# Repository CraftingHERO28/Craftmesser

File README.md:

# DIY Room Air Quality Monitor

I wanted to build a solid, reliable indoor air quality monitor to keep track of CO₂ levels, temperature, and humidity in my room. A lot of cheap commercial monitors use estimated VOC sensors instead of actual optical sensors, so I decided to design my own board around an Arduino Nano and an NDIR MH-Z19B sensor.

Through consistent through-hole (THT) construction and thermal decoupling, it delivers precise readings without self-heating distortion.

---

## How it Works & Hardware Choices

The setup is built completely with THT components on socket headers so everything stays easy to solder and swap out if needed:

* **Arduino Nano v3.x** handling the logic.
* **MH-Z19B** for actual NDIR CO₂ measurement.
* **DHT22 / AM2302** for temperature and humidity.
* **0.96" I2C OLED** for displaying live data.
* **Decoupling & Pull-up:** A `100nF` ceramic capacitor and a `100µF` electrolytic capacitor smooth out voltage drops when the CO₂ sensor warms up, paired with a `10kΩ` pull-up resistor for the DHT data line.

---

## Bill of Materials (BOM)

---

## Wiring Diagram

All components share a common `5V` and `GND` rail decoupled by the `100µF` electrolytic and `100nF` ceramic capacitors.

```text
                       +-----------------------+
                       |     ARDUINO NANO      |
                       |                       |
   +------------------>| 5V                 D2 |<---[10kΩ]---+--- 5V
   |   +-------------->| GND                   |             |
   |   |               |                    D3 |<---+        |
   |   |               |                    D4 |---+|        |
   |   |               |                    A4 |<--||---+    |
   |   |               |                    A5 |<--||--+|    |
   |   |               +-----------------------+   ||  ||    |
   |   |                                           ||  ||    |
   |   |   +---------------------------------------++  ||    |
   |   |   |   +---------------------------------------++    |
   |   |   |   |                                             |
   |   |   |   |       +-----------------------+             |
   |   |   |   |       |    DHT22 / AM2302     |             |
   +---|---|---|------>| VCC (Pin 1)           |             |
   |   |   |   |   +-->| DATA (Pin 2)          |<------------+
   |   +---|---|---|-->| GND (Pin 4)           |
   |   |   |   |   |   +-----------------------+
   |   |   |   |   |
   |   |   |   |   |   +-----------------------+
   |   |   |   |   |   |   MH-Z19B CO2 Sensor  |
   +---|---|---|------>| VIN (5V)              |
   |   +---|---|---|-->| GND                   |
   |   |   +---|---|-->| TX  (connects to D3)  |
   |   |   |   |   |   | RX  (connects to D4)  |
   |   |   |   |   |   +-----------------------+
   |   |   |   |   |
   |   |   |   |   |   +-----------------------+
   |   |   |   |   |   |   0.96" I2C OLED      |
   +---|---|---|------>| VCC                   |
   |   +---|---|---|-->| GND                   |
   |   |   |   +---|-->| SDA (connects to A4)  |
   |   |   |   |   +-->| SCL (connects to A5)  |
   |   |   |   |       +-----------------------+
   |   |   |   |
  [===] [===]  (Power Filtering across 5V & GND: 100µF Elko + 100nF Ceramic)
```

---

## How to Build It

### 1. Order the PCBs & Parts
* Export the Gerber files from the KiCad project and upload the `.zip` archive to **JLCPCB** (standard 2-layer FR4, 1.6mm thickness).
* Order all electronic components using the Reichelt links in the BOM table above.

### 2. Solder the Board (Lowest to Tallest)
1. **Passive Components:** Solder the `10kΩ` pull-up resistor and the `100nF` ceramic capacitor flat against the PCB.
2. **Socket Headers:** Solder the two `1x15` female headers for the Arduino Nano and the three `1x4` headers for the OLED, DHT22, and MH-Z19B. *Tip: Plug the headers onto the Arduino/modules first to keep them aligned while soldering.*
3. **Electrolytic Capacitor:** Solder the `100µF` capacitor into place, paying close attention to polarity (the striped side goes to `GND`).
4. **Insert Modules:** Once soldering is complete and checked for bridges, plug the Arduino Nano, OLED display, DHT22, and MH-Z19B into their respective sockets. Make sure the DHT22 sits cleanly at the edge of the board for accurate thermal isolation.

### 3. Flash the Firmware
1. Download and open the **Arduino IDE**.
2. Open the Library Manager (`Ctrl + Shift + I`) and install:
   * `Adafruit SSD1306`
   * `Adafruit GFX Library`
   * `DHT sensor library` (by Adafruit)
3. Connect the Arduino Nano via USB, select **Arduino Nano** (and **ATmega328P (Old Bootloader)** if using a clone) under *Tools*, and upload the firmware sketch.
4. After a 2-second boot screen, the OLED will display live CO₂ (ppm), temperature (°C), and humidity (%) readings.

---

## Design Notes & Things I Ran Into

* **Thermal Isolation:** The biggest challenge was keeping heat from the Arduino regulator and the CO₂ sensor away from the temperature reading. I ended up placing the DHT22 at the far corner of the PCB away from major trace paths.
* **Trace Routing:** I initially tried making decorative parallel power traces ("trace art"), but quickly realized it created routing clutter and unnecessary heat bridges toward the temp sensor. Going back to clean, single traces worked much better.
* **Edge Cuts:** I also experimented with slot cutouts on the PCB board outline (`Edge.Cuts`) for thermal isolation, but KiCad threw continuous DRC errors for open contours. Placing the sensor at the board edge using FR4's natural isolation turned out to be more than enough without messing with custom PCB millings.

_translated with google Translator_

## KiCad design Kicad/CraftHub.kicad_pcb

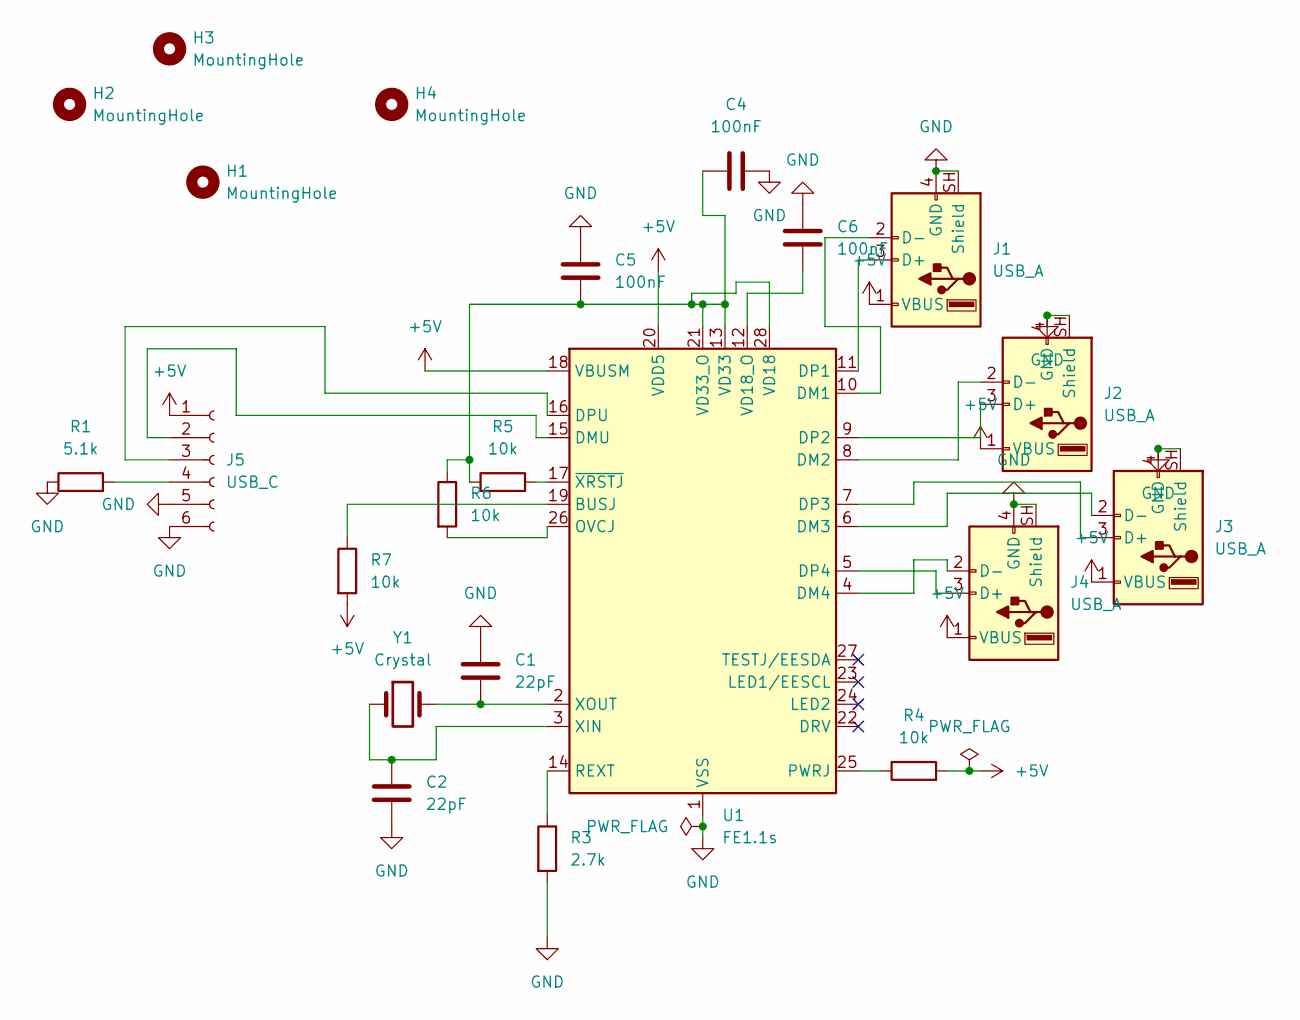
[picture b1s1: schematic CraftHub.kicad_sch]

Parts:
C1, C2: 22pF; C_Disc_D3.0mm_W1.6mm_P2.50mm
C4, C5, C6: 100nF; C_Disc_D3.0mm_W1.6mm_P2.50mm
H1, H2, H3, H4: MountingHole; MountingHole_2.2mm_M2
J1, J2, J3, J4: USB_A; USB_A_Molex_67643_Horizontal
J5: USB_C; PinHeader_1x06_P2.54mm_Vertical
R1: 5.1k; R_Axial_DIN0207_L6.3mm_D2.5mm_P7.62mm_Horizontal
R3: 2.7k; R_Axial_DIN0207_L6.3mm_D2.5mm_P7.62mm_Horizontal
R4, R5, R6, R7: 10k; R_Axial_DIN0207_L6.3mm_D2.5mm_P7.62mm_Horizontal
U1: FE1.1s; SSOP-28_3.9x9.9mm_P0.635mm
Y1: Crystal; Crystal_HC49-U_Vertical

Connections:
+5V: J1.1 (VBUS), J2.1 (VBUS), J3.1 (VBUS), J4.1 (VBUS), J5.1, R4.2, R7.2, U1.18 (VBUSM), U1.20 (VDD5)
GND: C1.1, C2.2, C4.2, C5.1, C6.1, J1.4 (GND), J1.SH (Shield), J2.4 (GND), J2.SH (Shield), J3.4 (GND), J3.SH (Shield), J4.4 (GND), J4.SH (Shield), J5.5, J5.6, R1.1, R3.2, U1.1 (VSS)
unnamed: J1.3 (D+), U1.11 (DP1)
unnamed: J1.2 (D-), U1.10 (DM1)
unnamed: J2.3 (D+), U1.9 (DP2)
unnamed: J2.2 (D-), U1.8 (DM2)
unnamed: J3.3 (D+), U1.7 (DP3)
unnamed: J3.2 (D-), U1.6 (DM3)
unnamed: J4.3 (D+), U1.5 (DP4)
unnamed: J4.2 (D-), U1.4 (DM4)
unnamed: J5.2, U1.15 (DMU)
unnamed: J5.3, U1.16 (DPU)
unnamed: J5.4, R1.2
unnamed: R7.1, U1.19 (BUSJ)
unnamed: R6.2, U1.26 (OVCJ)
unnamed: R4.1, U1.25 (PWRJ)
unnamed: R3.1, U1.14 (REXT)
unnamed: C4.1, C5.2, R5.1, R6.1, U1.13 (VD33), U1.21 (VD33_O), U1.28 (VD18)
unnamed: C6.2, U1.12 (VD18_O)
unnamed: C2.1, U1.3 (XIN), Y1.1
unnamed: C1.2, U1.2 (XOUT), Y1.2
unnamed: R5.2, U1.17 (~XRSTJ)

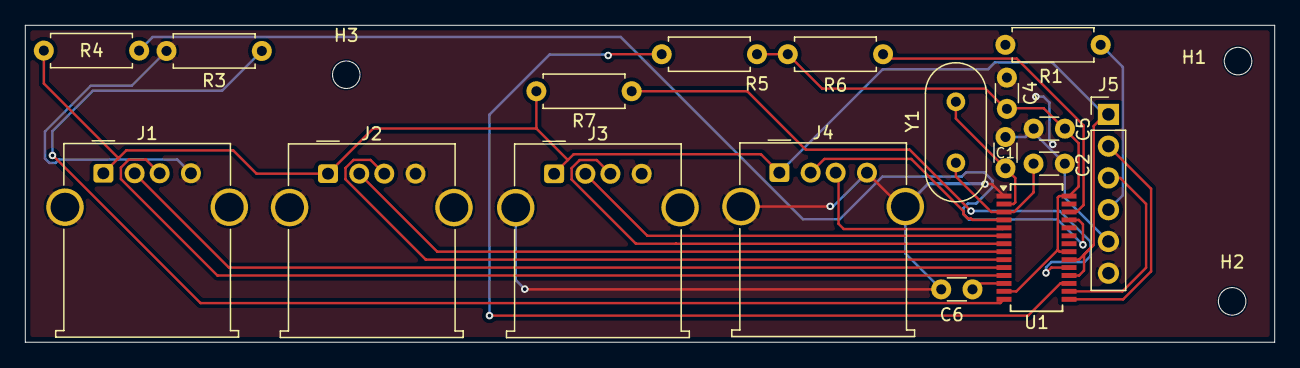
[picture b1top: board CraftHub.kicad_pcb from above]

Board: 2 copper layers, 99.9 x 25.3 mm, 21 parts (0 on the bottom side), 22 nets.

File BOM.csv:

Component,Value / Specification,Quantity,Link,Unit Price (€),Total Price (€),Notes
USB 2.0 Hub IC,FE1.1s (SSOP-28),1,https://www.amazon.de/gp/product/B0B9JZ5PLP/ref=ox_sc_act_ti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,2.5,2.5,"Core of the hub, consider SSOP-to-DIP adapter for manual soldering"
USB-C Connector,USB-C Breakout Bord,1,https://www.amazon.de/gp/product/B0H45QPTQ6/ref=ox_sc_act_ti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,7.57,7.57,Input / Upstream connection to PC
USB-A Connectors,USB-A Receptacle 90° THT ,4,https://www.reichelt.de/de/de/shop/produkt/usb-einbaubuchse_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,0.15,0.75,Outputs / Downstream ports for devices
Crystal,12 MHz HC-49U ,2,https://www.reichelt.de/de/de/shop/produkt/standardquarz_met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,0.27,0.54,Clock generator for the FE1.1s controller
Ceramic Capacitors,22pF,5,https://www.reichelt.de/de/de/shop/produkt/keramik-kondensat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,0.04,0.20,Load capacitors for the 12MHz crystal
Decoupling Capacitors,100nF ,5,https://www.reichelt.de/de/de/shop/produkt/vielschicht-kerko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,0.05,0.25,Bypass capacitors at VCC pins
Resistors,10/5.1/2.7k Ohm ,10/5/10,https://www.reichelt.de/de/de/shop/produkt/duennschichtwider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,0.05/0.09/0.042,1.37,Pull-up / configuration resistors
6 Pin Header,6 Pin Header,1,https://www.reichelt.de/de/de/shop/produkt/stiftleisten_2_54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,0.33,0.33,Pin Header to connect the USB-C Board to the PCB
Printed Circuit Board (PCB),Custom 2-Layer PCB,1,https://jlcpcb.com,4.5,4.5,Manufacturing cost for 5 PCBs
Shipping (Components),Amazon/Reichelt,2,,11.5/6,17.5,Postage for electronic components
Shipping (JLCPCB PCB),Standard Shipping,1,,1.4,1.4,Shipping of PCBs/3D from China
Tax and Fee,Tax and Fee for shipping to EU (JLCPBC),1,,6.0,6.0,Shipping of PCBs/3D to EU
TOTAL,ca. EUR: 42.91 € | USD: $47.24,,,,,

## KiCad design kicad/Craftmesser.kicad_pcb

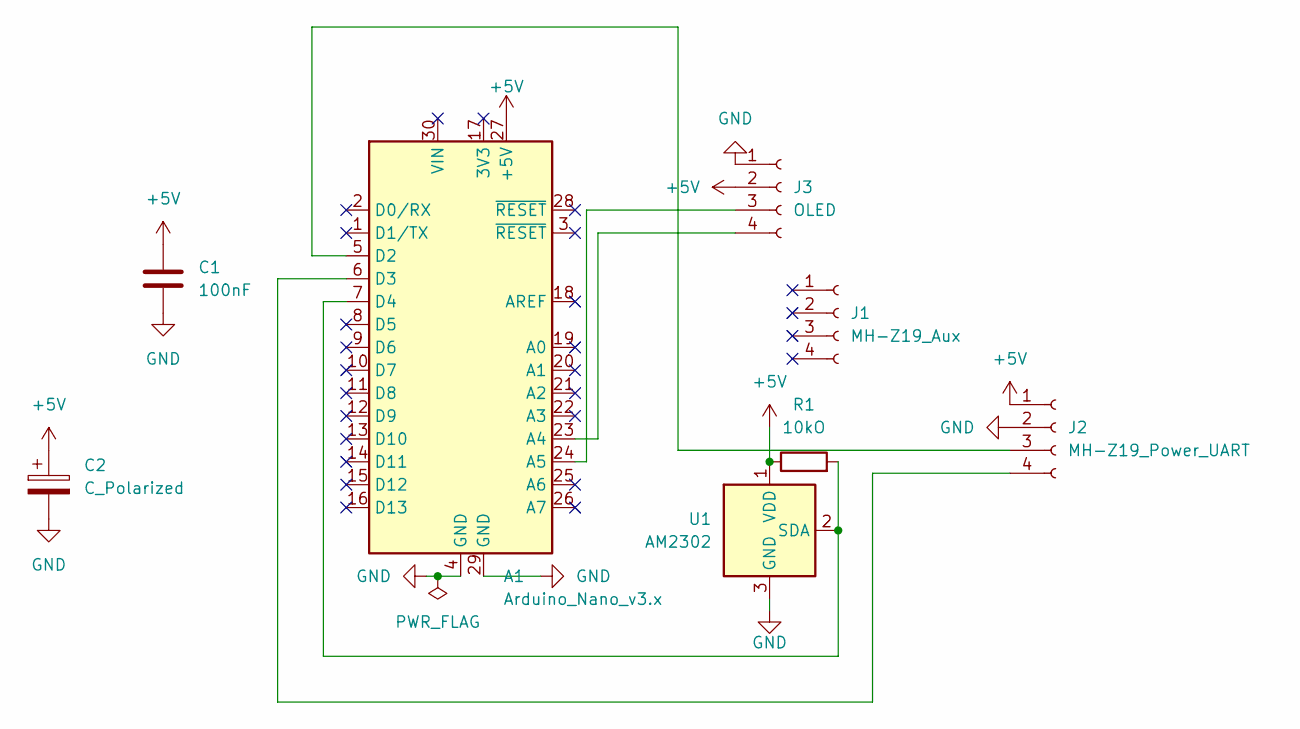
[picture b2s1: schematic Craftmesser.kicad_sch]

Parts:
A1: Arduino_Nano_v3.x; Arduino_Nano
C1: 100nF; C_Disc_D5.0mm_W2.5mm_P5.00mm
C2: C_Polarized; CP_Radial_D6.3mm_P2.50mm
J1: MH-Z19_Aux; PinHeader_1x04_P2.54mm_Vertical
J2: MH-Z19_Power_UART; PinHeader_1x04_P2.54mm_Vertical
J3: OLED; PinHeader_1x04_P2.54mm_Vertical
R1: 10kO; R_Axial_DIN0207_L6.3mm_D2.5mm_P7.62mm_Horizontal
U1: AM2302; ASAIR_AM2302_P2.54mm_Vertical

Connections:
+5V: A1.27 (+5V), C1.1, C2.1, J2.1, J3.2, R1.1, U1.1 (VDD)
GND: A1.4 (GND), A1.29 (GND), C1.2, C2.2, J2.2, J3.1, U1.3 (GND), U1.4 (GND)
unnamed: A1.23 (A4), J3.4
unnamed: A1.24 (A5), J3.3
unnamed: A1.5 (D2), J2.3
unnamed: A1.6 (D3), J2.4
unnamed: A1.7 (D4), R1.2, U1.2 (SDA)

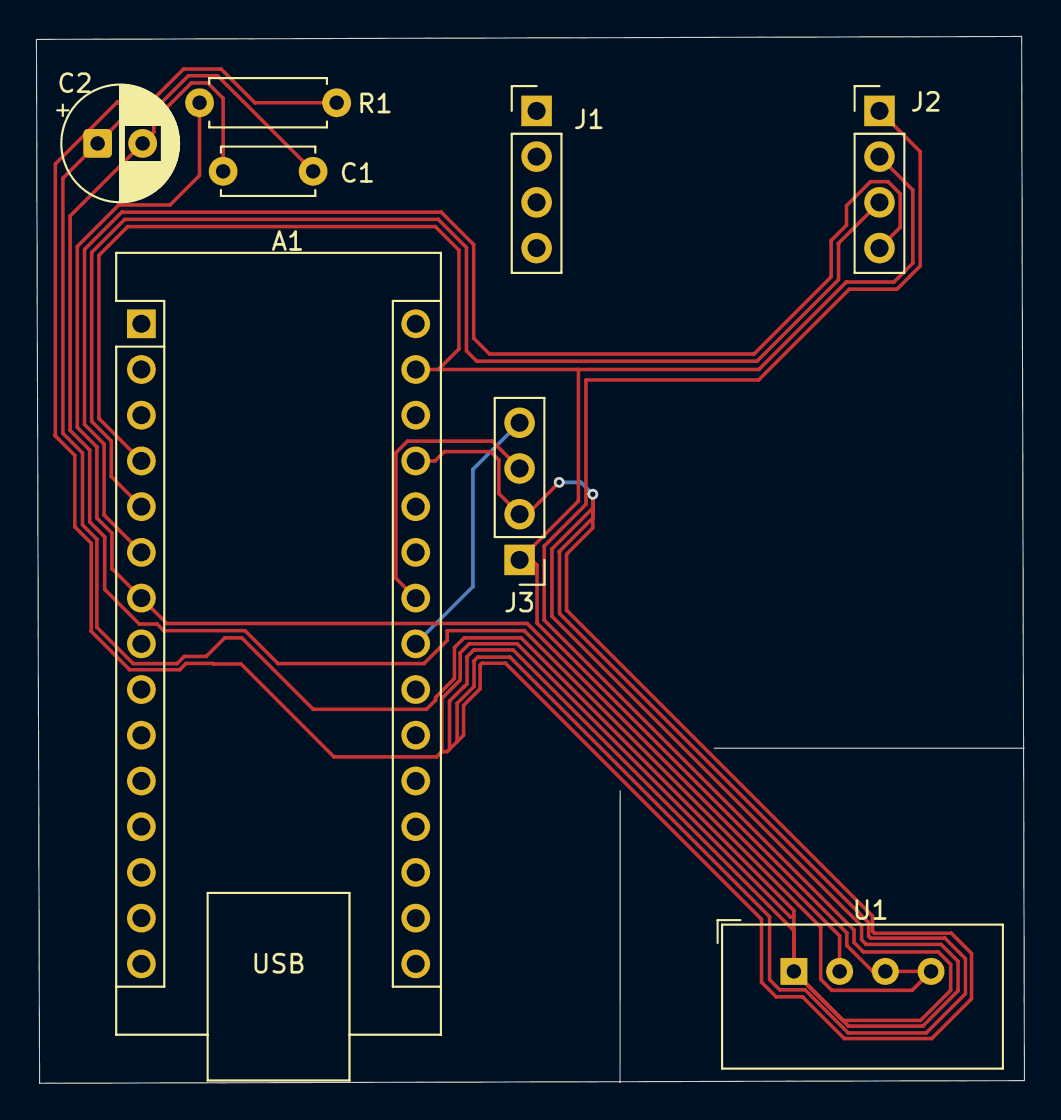
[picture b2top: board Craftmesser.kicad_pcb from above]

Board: 2 copper layers, 54.9 x 58.2 mm, 8 parts (0 on the bottom side), 7 nets.
